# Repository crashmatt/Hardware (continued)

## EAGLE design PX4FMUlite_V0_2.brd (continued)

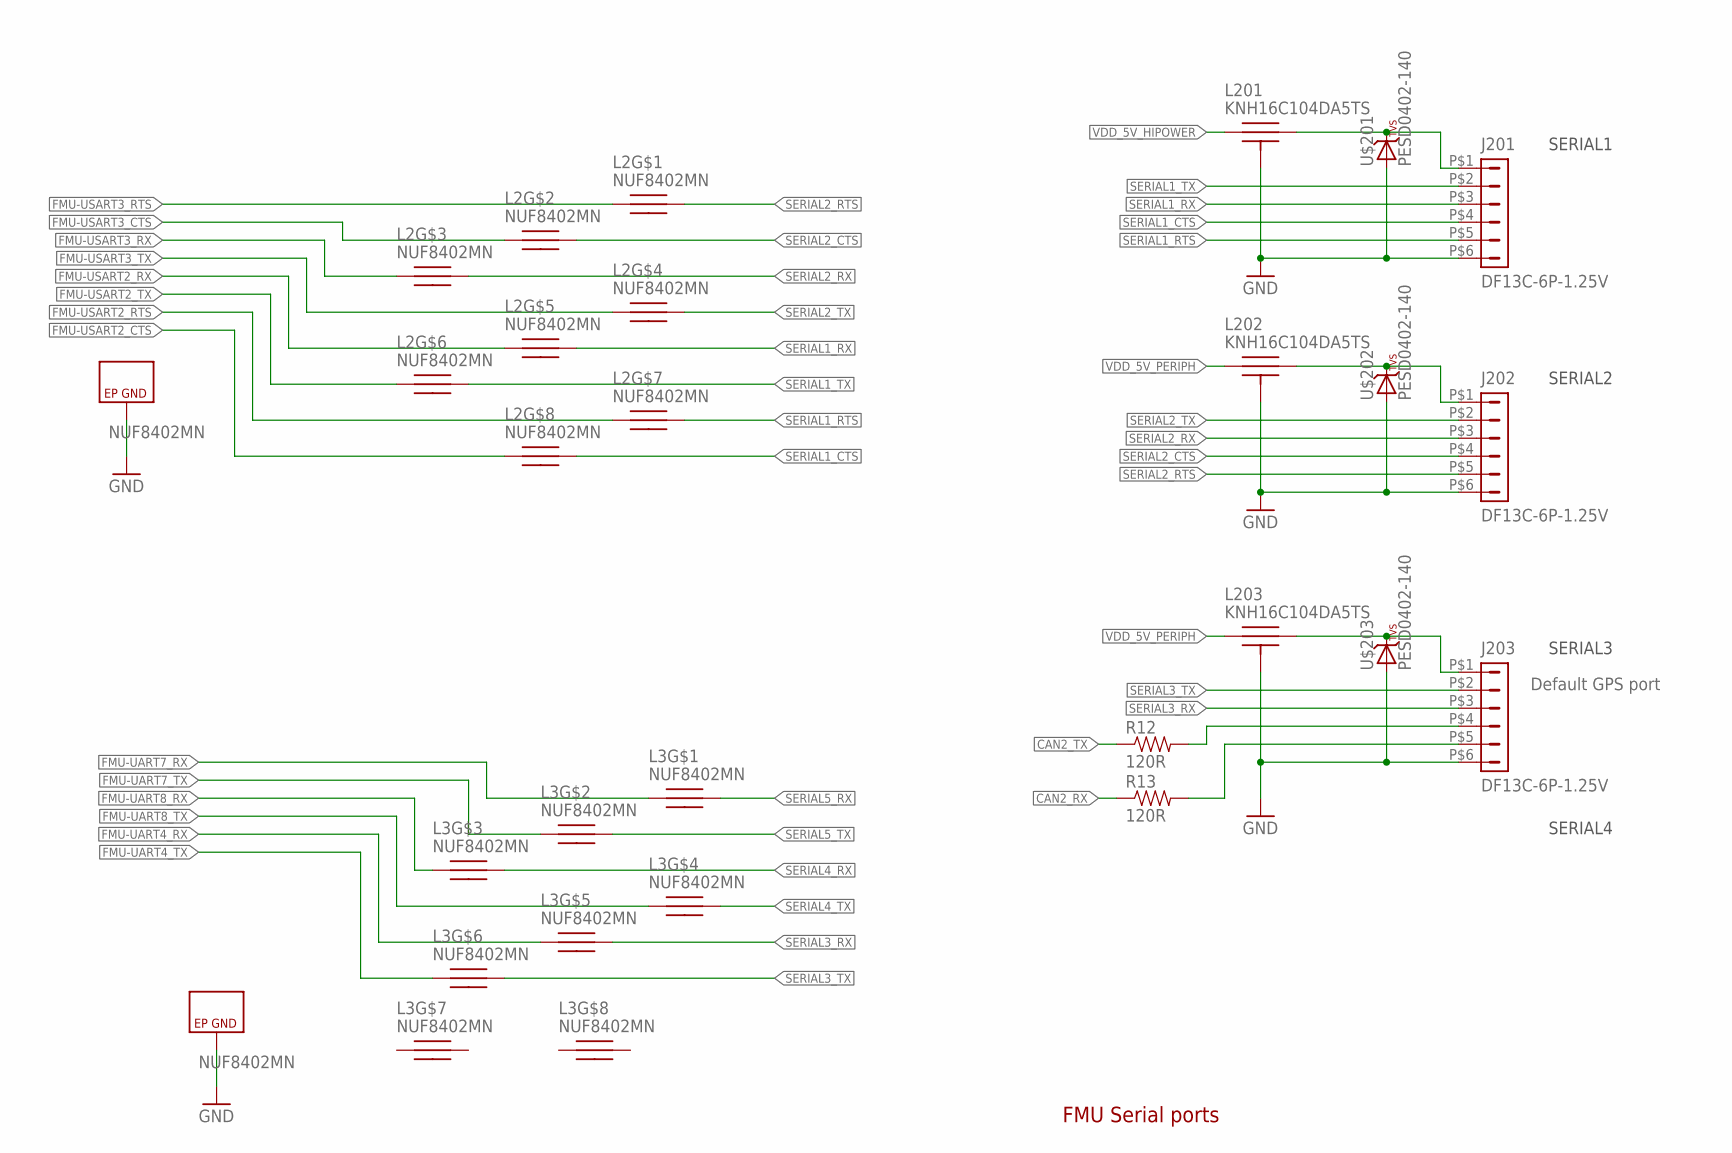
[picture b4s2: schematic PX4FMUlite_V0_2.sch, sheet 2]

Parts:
J201, J202, J203: DF13C-6P-1.25V; PARTNO DF13C-6P-1.25V(20)
L2, L3: NUF8402MN; DFN16-THIN
L201, L202, L203: KNH16C104DA5TS; KYOCERA-KNH16-DA; PARTNO KNH16C104DA5TS
R12, R13: 120R; 0402-RES; PARTNO RC0402FR-07120RL
U$201, U$202, U$203: PESD0402-140; 0402-TVS; PARTNO PESD0402-140

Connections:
CAN2_RX: R13.P$1 (1); also elsewhere on the board
CAN2_TX: R12.P$1 (1); also elsewhere on the board
FMU-UART4_RX: L3.P$5; also elsewhere on the board
FMU-UART4_TX: L3.P$6; also elsewhere on the board
FMU-UART7_RX: L3.P$1; also elsewhere on the board
FMU-UART7_TX: L3.P$2; also elsewhere on the board
FMU-UART8_RX: L3.P$3; also elsewhere on the board
FMU-UART8_TX: L3.P$4; also elsewhere on the board
FMU-USART2_CTS: L2.P$8; also elsewhere on the board
FMU-USART2_RTS: L2.P$7; also elsewhere on the board
FMU-USART2_RX: L2.P$5; also elsewhere on the board
FMU-USART2_TX: L2.P$6; also elsewhere on the board
FMU-USART3_CTS: L2.P$2; also elsewhere on the board
FMU-USART3_RTS: L2.P$1; also elsewhere on the board
FMU-USART3_RX: L2.P$3; also elsewhere on the board
FMU-USART3_TX: L2.P$4; also elsewhere on the board
GND: L2.P$EP (GND), L3.P$EP (GND); also elsewhere on the board
GNDX: J201.P$6 (6), J202.P$6 (6), J203.P$6 (6), L201.P$3, L201.P$4, L201.P$5, L202.P$3, L202.P$4, L202.P$5, L203.P$3, L203.P$4, L203.P$5, U$201.A, U$202.A, U$203.A; also elsewhere on the board
unnamed: J201.P$1 (1), L201.P$2, U$201.C
unnamed: J203.P$4 (4), R12.P$2 (2)
unnamed: J203.P$5 (5), R13.P$2 (2)
unnamed: J203.P$1 (1), L203.P$2, U$203.C
unnamed: J202.P$1 (1), L202.P$2, U$202.C
SERIAL1_CTS: J201.P$4 (4), L2.P$9
SERIAL1_RTS: J201.P$5 (5), L2.P$10
SERIAL1_RX: J201.P$3 (3), L2.P$12; also elsewhere on the board
SERIAL1_TX: J201.P$2 (2), L2.P$11; also elsewhere on the board
SERIAL2_CTS: J202.P$4 (4), L2.P$15
SERIAL2_RTS: J202.P$5 (5), L2.P$16
SERIAL2_RX: J202.P$3 (3), L2.P$14; also elsewhere on the board
SERIAL2_TX: J202.P$2 (2), L2.P$13; also elsewhere on the board
SERIAL3_RX: J203.P$3 (3), L3.P$12; also elsewhere on the board
SERIAL3_TX: J203.P$2 (2), L3.P$11; also elsewhere on the board
SERIAL4_RX: L3.P$14; also elsewhere on the board
SERIAL4_TX: L3.P$13; also elsewhere on the board
SERIAL5_RX: L3.P$16; also elsewhere on the board
SERIAL5_TX: L3.P$15; also elsewhere on the board
VDD_5V_HIPOWER: L201.P$1
VDD_5V_PERIPH: L202.P$1, L203.P$1; also elsewhere on the board

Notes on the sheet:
FMU Serial ports
SERIAL2
SERIAL1
SERIAL3
SERIAL4
Default GPS port

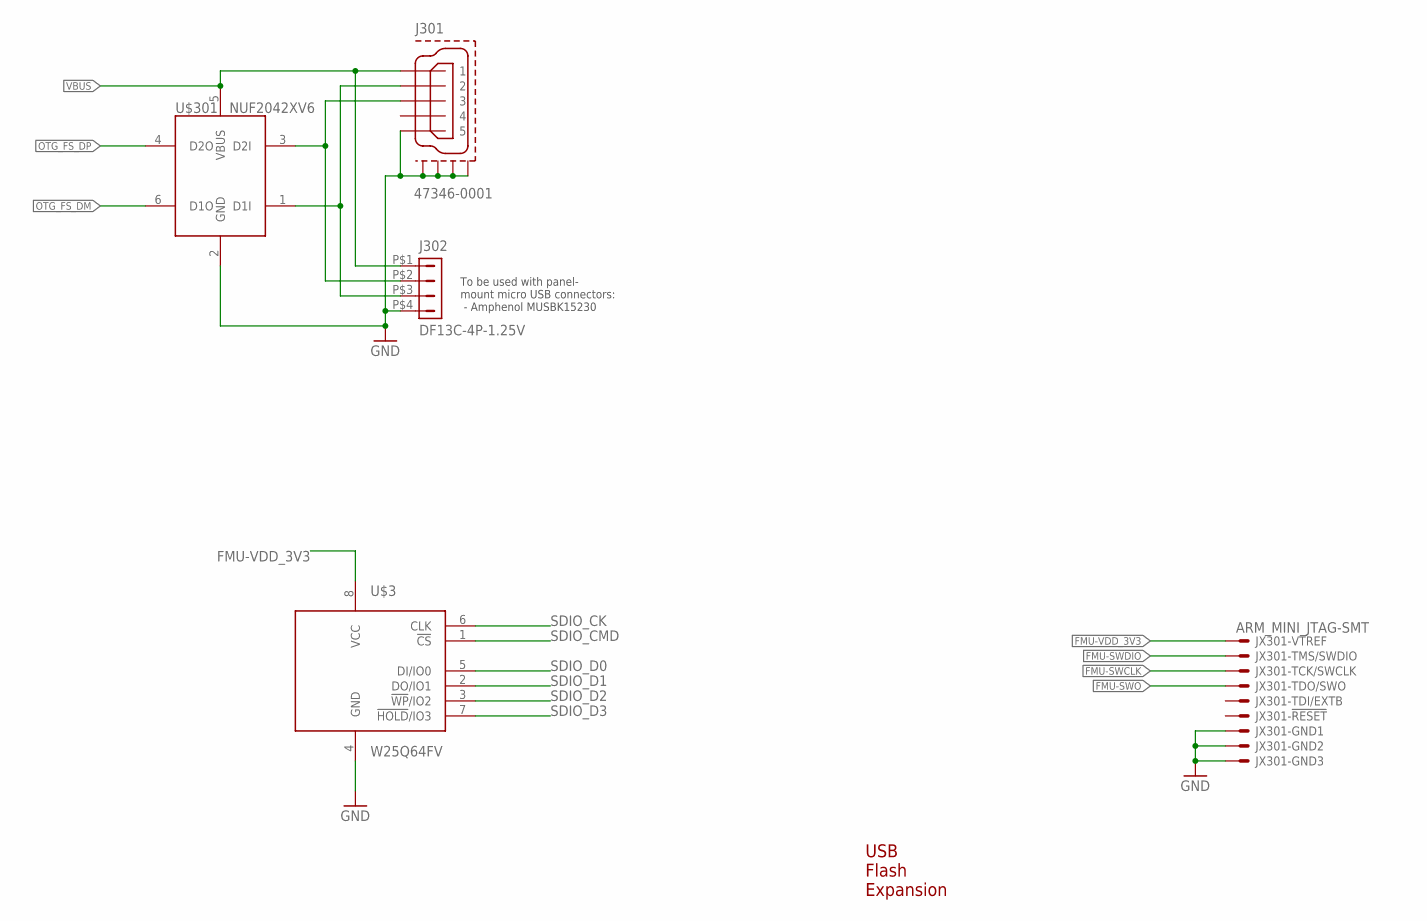
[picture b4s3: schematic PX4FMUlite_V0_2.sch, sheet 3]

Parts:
J301: 47346-0001; MOLEX-47346-0001; PARTNO 47346-0001
J302: DF13C-4P-1.25V; PARTNO DF13C-4P-1.25V(20)
JX301: ARM_MINI_JTAG-SMT; FTSH-105-01-XXX-DV-K; PARTNO M50-3900542
U$3: W25Q64FV; WSON-8-5X6
U$301: NUF2042XV6; SOT563-6; PARTNO NUF2042XV6T1G

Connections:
FMU-SWCLK: JX301.4; also elsewhere on the board
FMU-SWDIO: JX301.2; also elsewhere on the board
FMU-SWO: JX301.6; also elsewhere on the board
FMU-VDD_3V3: JX301.1, U$3.8 (VCC); also elsewhere on the board
GND: U$3.4 (GND); also elsewhere on the board
GNDX: J301.GND (5), J301.GND1, J301.GND2, J301.GND3, J301.GND4, J302.P$4 (4), JX301.3, JX301.5, JX301.9, U$301.2 (GND); also elsewhere on the board
OTG_DM1: J301.D- (2), J302.P$3 (3), U$301.1 (D1I)
OTG_DP1: J301.D+ (3), J302.P$2 (2), U$301.3 (D2I)
OTG_FS_DM: U$301.6 (D1O); also elsewhere on the board
OTG_FS_DP: U$301.4 (D2O); also elsewhere on the board
SDIO_CK: U$3.6 (CLK); also elsewhere on the board
SDIO_CMD: U$3.1 (!CS); also elsewhere on the board
SDIO_D0: U$3.5 (DI/IO0); also elsewhere on the board
SDIO_D1: U$3.2 (DO/IO1); also elsewhere on the board
SDIO_D2: U$3.3 (!WP!/IO2); also elsewhere on the board
SDIO_D3: U$3.7 (!HOLD!/IO3); also elsewhere on the board
VBUS: J301.VBUS (1), J302.P$1 (1), U$301.5 (VBUS); also elsewhere on the board

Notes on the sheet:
USB Flash Expansion
To be used with panel- mount micro USB connectors: - Amphenol MUSBK15230

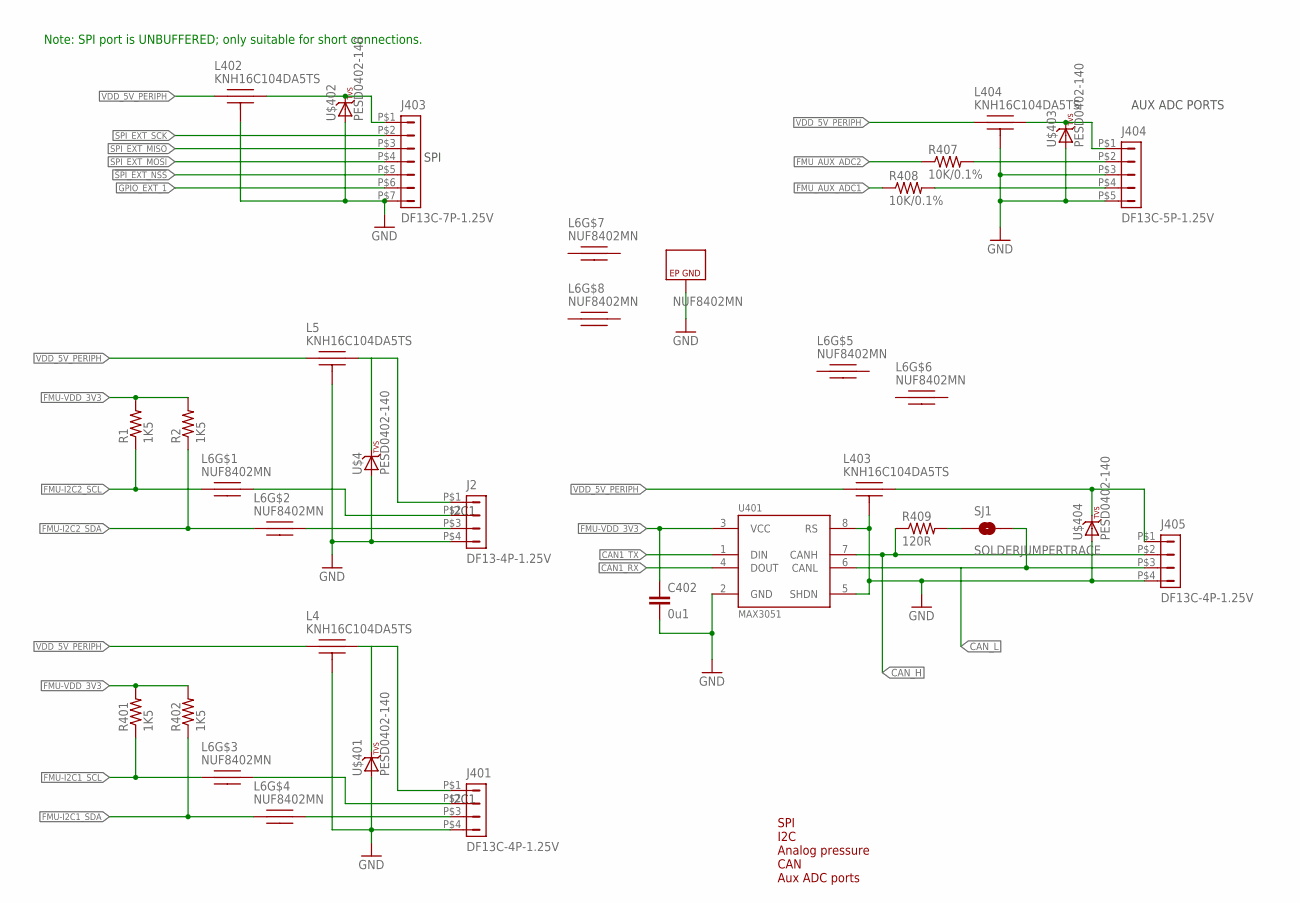
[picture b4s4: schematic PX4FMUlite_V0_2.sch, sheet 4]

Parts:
C402: 0u1; 0402-CAP; PARTNO CC0402ZRY5V7BB104
J2: DF13-4P-1.25V; DF13C-4P-1.25V; PARTNO DF13C-4P-1.25V(20)
J401, J405: DF13C-4P-1.25V; PARTNO DF13C-4P-1.25V(20)
J403: DF13C-7P-1.25V; PARTNO DF13C-7P-1.25V(20)
J404: DF13C-5P-1.25V; PARTNO DF13C-5P-1.25V(20)
L4, L5, L402, L403, L404: KNH16C104DA5TS; KYOCERA-KNH16-DA; PARTNO KNH16C104DA5TS
L6: NUF8402MN; DFN16-THIN
R1, R2, R401, R402: 1K5; 0402-RES; PARTNO RC0402FR-071K5L
R407, R408: 10K/0.1%; 0402-RES; PARTNO ERA-2AEB103X
R409: 120R; 0402-RES; PARTNO RC0402FR-07120RL
SJ1: SOLDERJUMPERTRACE; SJ_2S-TRACE
U401: MAX3051; SOT23-8; PARTNO MAX3051EKA
U$4, U$401, U$402, U$403, U$404: PESD0402-140; 0402-TVS; PARTNO PESD0402-140

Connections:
!SPI_EXT_NSS: J403.P$5 (5); also elsewhere on the board
CAN1_RX: U401.4 (DOUT); also elsewhere on the board
CAN1_TX: U401.1 (DIN); also elsewhere on the board
CAN_H: J405.P$2 (2), R409.P$1 (1), U401.7 (CANH); also elsewhere on the board
CAN_L: J405.P$3 (3), SJ1.2, U401.6 (CANL); also elsewhere on the board
FMU-I2C1_SCL: L6.P$3, R401.P$1 (1); also elsewhere on the board
FMU-I2C1_SDA: L6.P$4, R402.P$1 (1); also elsewhere on the board
FMU-I2C2_SCL: L6.P$1, R1.P$1 (1); also elsewhere on the board
FMU-I2C2_SDA: L6.P$2, R2.P$1 (1); also elsewhere on the board
FMU-VDD_3V3: C402.P$1 (1), R1.P$2 (2), R2.P$2 (2), R401.P$2 (2), R402.P$2 (2), U401.3 (VCC); also elsewhere on the board
FMU_AUX_ADC1: R408.P$1 (1); also elsewhere on the board
FMU_AUX_ADC1_PROT: J404.P$4 (4), R408.P$2 (2)
FMU_AUX_ADC2: R407.P$1 (1); also elsewhere on the board
FMU_AUX_ADC2_PROT: J404.P$2 (2), R407.P$2 (2)
GND: J2.P$4 (4), L5.P$3, L5.P$4, L5.P$5, U$4.A; also elsewhere on the board
GNDX: C402.P$2 (2), J401.P$4 (4), J403.P$7 (7), J404.P$3 (3), J404.P$5 (5), J405.P$4 (4), L4.P$3, L4.P$4, L4.P$5, L6.P$EP (GND), L402.P$3, L402.P$4, L402.P$5, L403.P$3, L403.P$4, L403.P$5, L404.P$3, L404.P$4, L404.P$5, U401.2 (GND), U401.5 (SHDN), U401.8 (RS), U$401.A, U$402.A, U$403.A, U$404.A; also elsewhere on the board
GPIO_EXT_1: J403.P$6 (6); also elsewhere on the board
unnamed: J2.P$2 (2), L6.P$16
unnamed: J2.P$3 (3), L6.P$15
unnamed: J2.P$1 (1), L5.P$2, U$4.C
unnamed: R409.P$2 (2), SJ1.1
unnamed: J401.P$2 (2), L6.P$14
unnamed: J401.P$3 (3), L6.P$13
unnamed: J403.P$1 (1), L402.P$2, U$402.C
unnamed: J401.P$1 (1), L4.P$2, U$401.C
unnamed: J405.P$1 (1), L403.P$2, U$404.C
unnamed: J404.P$1 (1), L404.P$2, U$403.C
SPI_EXT_MISO: J403.P$3 (3); also elsewhere on the board
SPI_EXT_MOSI: J403.P$4 (4); also elsewhere on the board
SPI_EXT_SCK: J403.P$2 (2); also elsewhere on the board
VDD_5V_PERIPH: L402.P$1, L403.P$1, L404.P$1; also elsewhere on the board

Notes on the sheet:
SPI
I2C1
AUX ADC PORTS
SPI I2C Analog pressure CAN Aux ADC ports
Note: SPI port is UNBUFFERED; only suitable for short connections.

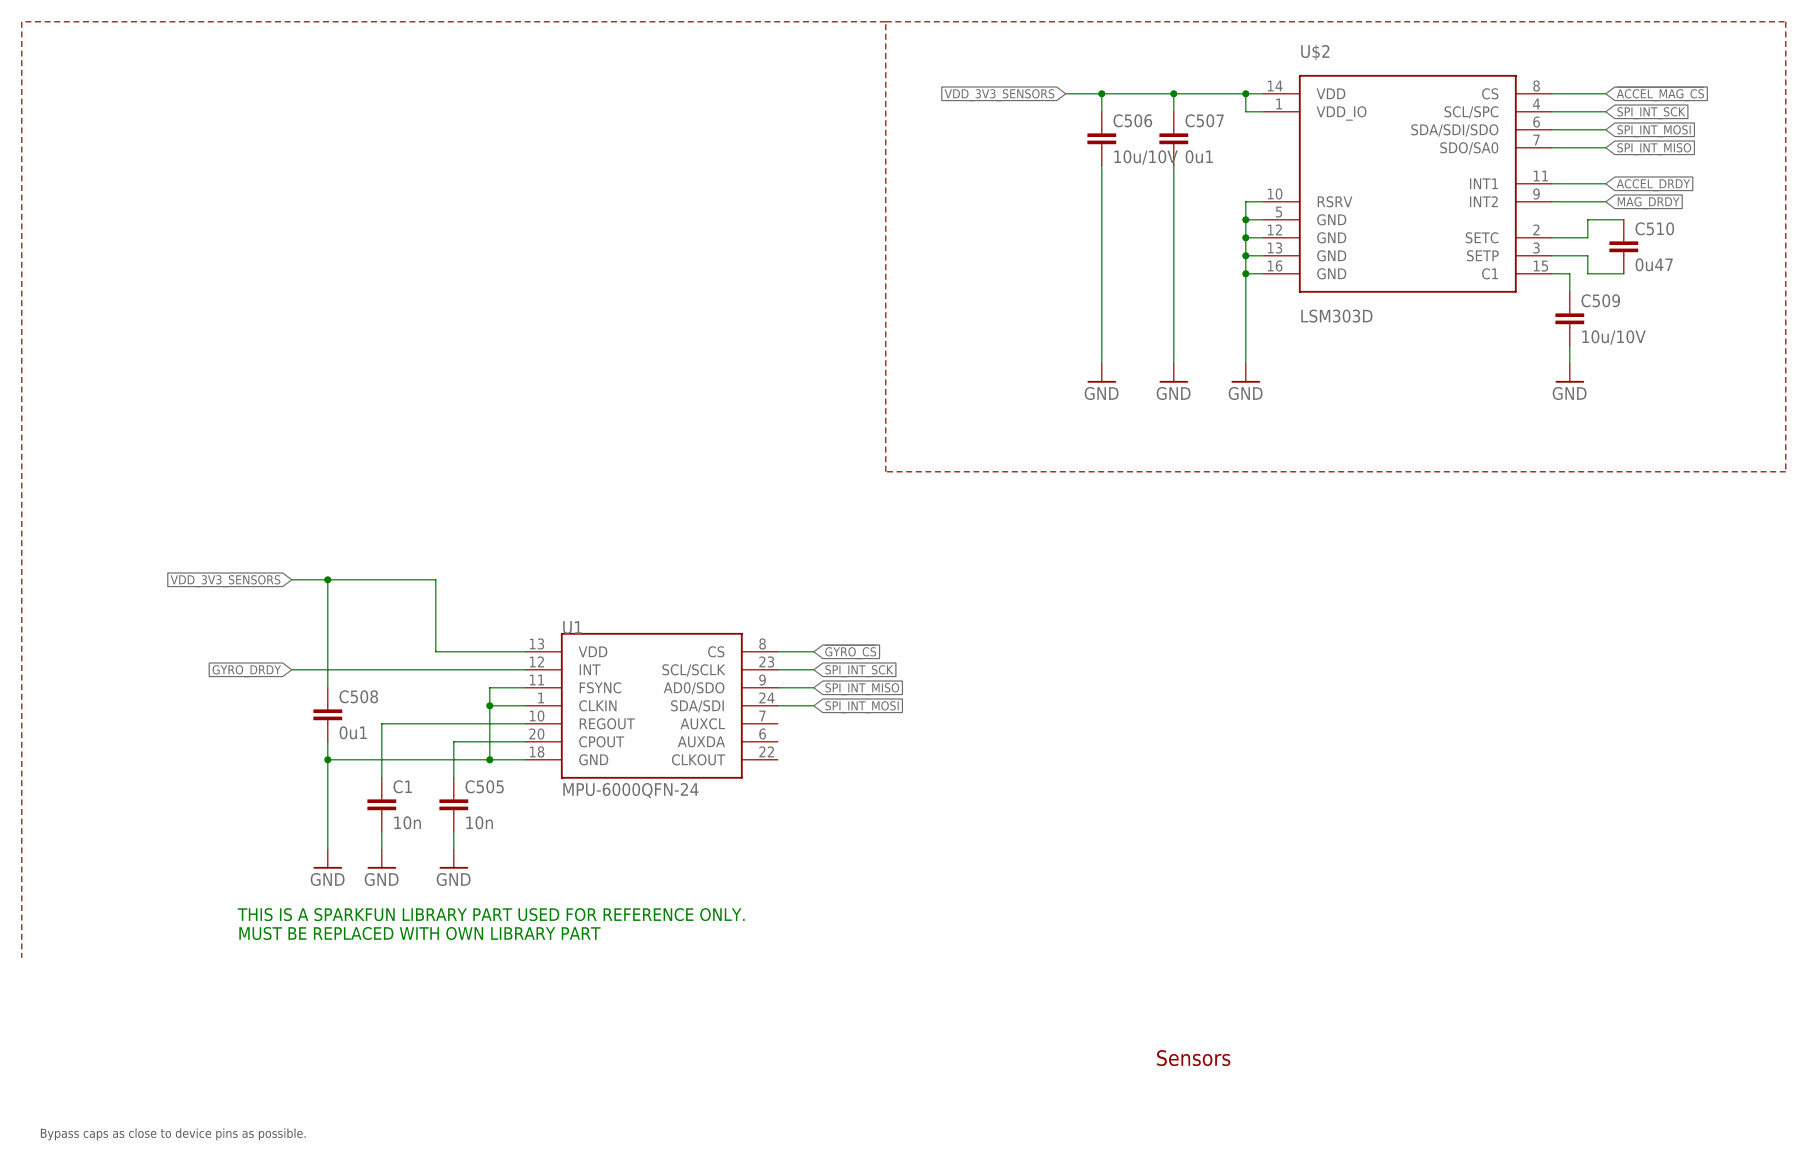
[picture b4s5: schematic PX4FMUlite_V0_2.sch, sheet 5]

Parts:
C1, C505: 10n; 0402-CAP; PARTNO CC0402KRX7R7BB103
C506, C509: 10u/10V; 0805-CAP; PARTNO CC0805ZKY5V6BB106
C507, C508: 0u1; 0402-CAP; PARTNO CC0402ZRY5V7BB104
C510: 0u47; 0402-CAP; PARTNO C1005X5R1C474K050BC
U1: MPU-6000QFN-24; QFN-24-TESTING
U$2: LSM303D; LGA-16L

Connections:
!ACCEL_MAG_CS: U$2.8 (CS); also elsewhere on the board
!GYRO_CS: U1.8 (CS); also elsewhere on the board
ACCEL_DRDY: U$2.11 (INT1); also elsewhere on the board
GND: C1.P$2 (2); also elsewhere on the board
GNDX: C505.P$2 (2), C506.P$2 (2), C507.P$2 (2), C508.P$2 (2), C509.P$2 (2), U1.1 (CLKIN), U1.11 (FSYNC), U1.18 (GND), U$2.5 (GND), U$2.10 (RSRV), U$2.12 (GND), U$2.13 (GND), U$2.16 (GND); also elsewhere on the board
GYRO_DRDY: U1.12 (INT); also elsewhere on the board
MAG_DRDY: U$2.9 (INT2); also elsewhere on the board
unnamed: C509.P$1 (1), U$2.15 (C1)
unnamed: C510.P$1 (1), U$2.2 (SETC)
unnamed: C510.P$2 (2), U$2.3 (SETP)
unnamed: C505.P$1 (1), U1.20 (CPOUT)
unnamed: C1.P$1 (1), U1.10 (REGOUT)
SPI_INT_MISO: U1.9 (AD0/SDO), U$2.7 (SDO/SA0); also elsewhere on the board
SPI_INT_MOSI: U1.24 (SDA/SDI), U$2.6 (SDA/SDI/SDO); also elsewhere on the board
SPI_INT_SCK: U1.23 (SCL/SCLK), U$2.4 (SCL/SPC); also elsewhere on the board
VDD_3V3_SENSORS: C506.P$1 (1), C507.P$1 (1), C508.P$1 (1), U1.13 (VDD), U$2.1 (VDD_IO), U$2.14 (VDD); also elsewhere on the board

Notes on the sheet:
Sensors
Bypass caps as close to device pins as possible.
THIS IS A SPARKFUN LIBRARY PART USED FOR REFERENCE ONLY. MUST BE REPLACED WITH OWN LIBRARY PART

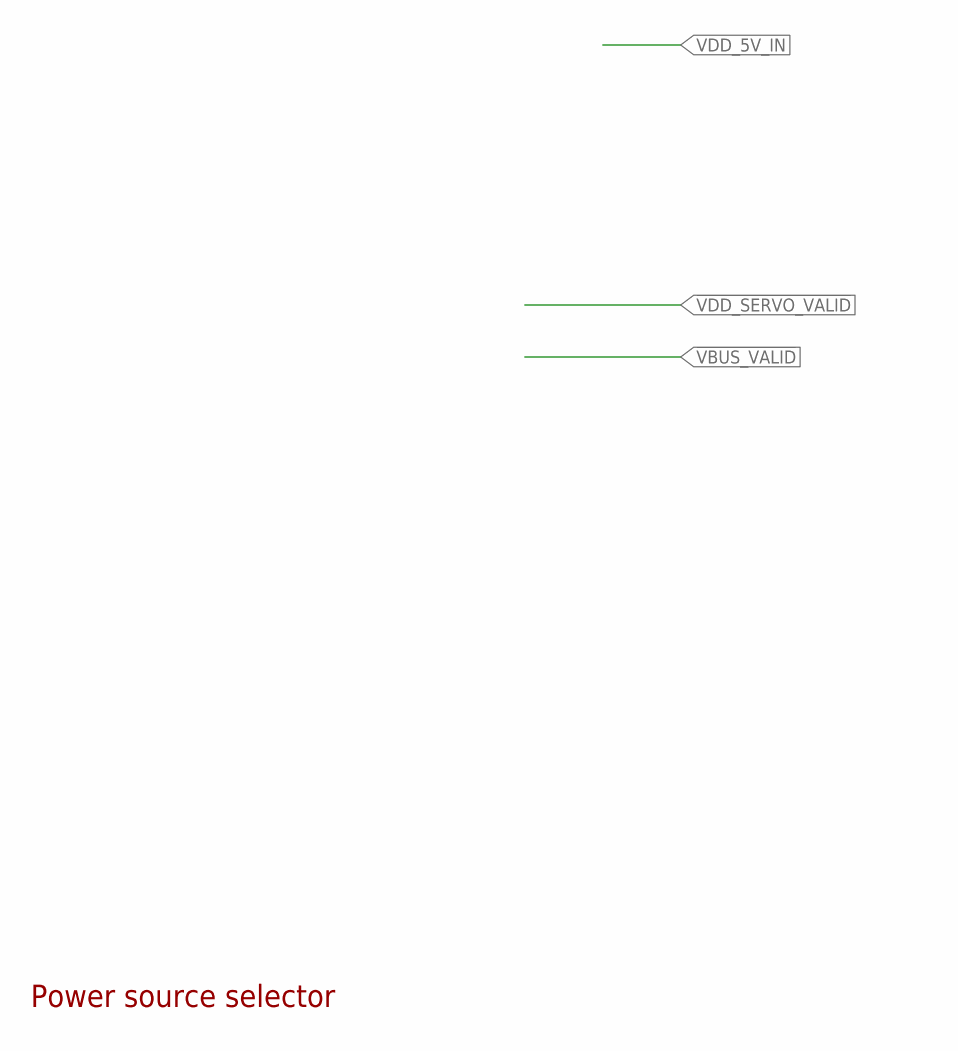
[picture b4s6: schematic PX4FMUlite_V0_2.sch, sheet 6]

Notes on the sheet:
Power source selector

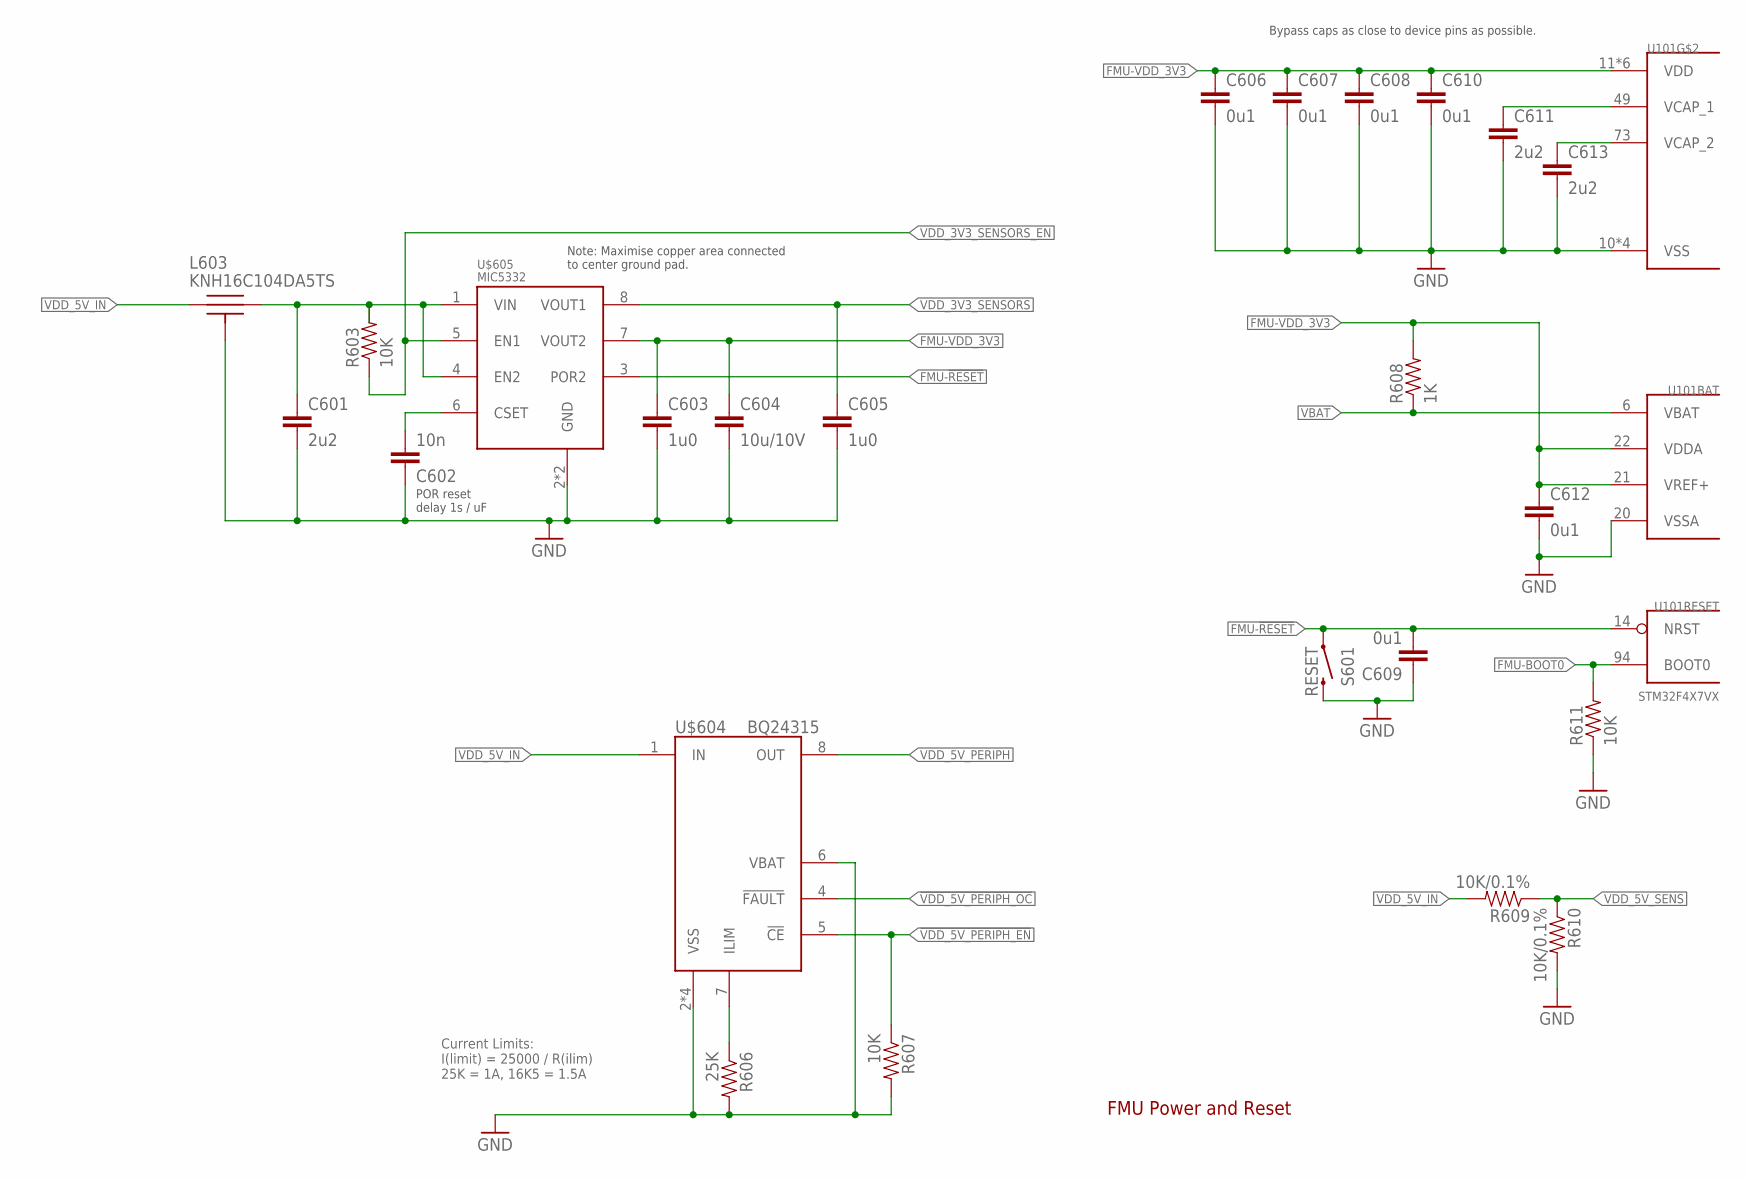
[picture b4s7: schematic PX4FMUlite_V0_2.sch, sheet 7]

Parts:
C601, C611, C613: 2u2; 0603-CAP; PARTNO C1608Y5V1C225Z
C602: 10n; 0402-CAP; PARTNO CC0402KRX7R7BB103
C603, C605: 1u0; 0603-CAP; PARTNO CC0603ZRY5V7BB105
C604: 10u/10V; 0805-CAP; PARTNO CC0805ZKY5V6BB106
C606, C607, C608, C609, C610, C612: 0u1; 0402-CAP; PARTNO CC0402ZRY5V7BB104
L603: KNH16C104DA5TS; KYOCERA-KNH16-DA; PARTNO KNH16C104DA5TS
R603, R607, R611: 10K; 0402-RES; PARTNO RC0402FR-0710KL
R606: 25K; 0402-RES; PARTNO RMCF0402FT25K5
R608: 1K; 0402-RES; PARTNO RC0402FR-071KL
R609, R610: 10K/0.1%; 0402-RES; PARTNO ERA-2AEB103X
S601: RESET; EVQP7J01K; PARTNO EVQP7J01K
U101: STM32F4X7VX; TQFP100; PARTNO STM32F427VI
U$604: BQ24315; QFN8-DSG; PARTNO BQ24315DSGR
U$605: MIC5332; MLF-8-EPAD; PARTNO MIC5332-SSYMT

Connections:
!VDD_5V_PERIPH_EN: R607.P$1 (1), U$604.5 (!CE); also elsewhere on the board
!VDD_5V_PERIPH_OC: U$604.4 (!FAULT); also elsewhere on the board
FMU-!RESET: C609.P$2 (2), S601.A1 (1), U101.14 (NRST), U$605.3 (POR2)
FMU-BOOT0: R611.P$2 (2), U101.94 (BOOT0); also elsewhere on the board
FMU-VDD_3V3: C603.P$1 (1), C604.P$1 (1), C606.P$1 (1), C607.P$1 (1), C608.P$1 (1), C610.P$1 (1), C612.P$1 (1), R608.P$2 (2), U101.11 (VDD), U101.19 (VDD), U101.21 (VREF+), U101.22 (VDDA), U101.28 (VDD), U101.50 (VDD), U101.75 (VDD), U101.100 (VDD), U$605.7 (VOUT2); also elsewhere on the board
FMU-VDD_5V5: C601.P$1 (1), L603.P$2, R603.P$2 (2), U$605.1 (VIN), U$605.4 (EN2)
GNDX: C601.P$2 (2), C602.P$1 (1), C603.P$2 (2), C604.P$2 (2), C605.P$2 (2), C606.P$2 (2), C607.P$2 (2), C608.P$2 (2), C609.P$1 (1), C610.P$2 (2), C611.P$2 (2), C612.P$2 (2), C613.P$2 (2), L603.P$3, L603.P$4, L603.P$5, R606.P$2 (2), R607.P$2 (2), R610.P$2 (2), R611.P$1 (1), S601.B3 (2), U101.10 (VSS), U101.20 (VSSA), U101.27 (VSS), U101.74 (VSS), U101.99 (VSS), U$604.2 (VSS), U$604.6 (VBAT), U$604.GND (VSS), U$604.P$2 (VSS), U$604.P$3 (VSS), U$605.2 (GND), U$605.GND; also elsewhere on the board
unnamed: C613.P$1 (1), U101.73 (VCAP_2)
unnamed: C602.P$2 (2), U$605.6 (CSET)
unnamed: C611.P$1 (1), U101.49 (VCAP_1)
unnamed: R606.P$1 (1), U$604.7 (ILIM)
VBAT: R608.P$1 (1), U101.6 (VBAT)
VDD_3V3_SENSORS: C605.P$1 (1), U$605.8 (VOUT1); also elsewhere on the board
VDD_3V3_SENSORS_EN: R603.P$1 (1), U$605.5 (EN1); also elsewhere on the board
VDD_5V_IN: L603.P$1, R609.P$2 (2), U$604.1 (IN)
VDD_5V_PERIPH: U$604.8 (OUT); also elsewhere on the board
VDD_5V_SENS: R609.P$1 (1), R610.P$1 (1); also elsewhere on the board

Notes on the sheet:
FMU Power and Reset
Bypass caps as close to device pins as possible.
Note: Maximise copper area connected to center ground pad.
POR reset delay 1s / uF
Current Limits: I(limit) = 25000 / R(ilim) 25K = 1A, 16K5 = 1.5A

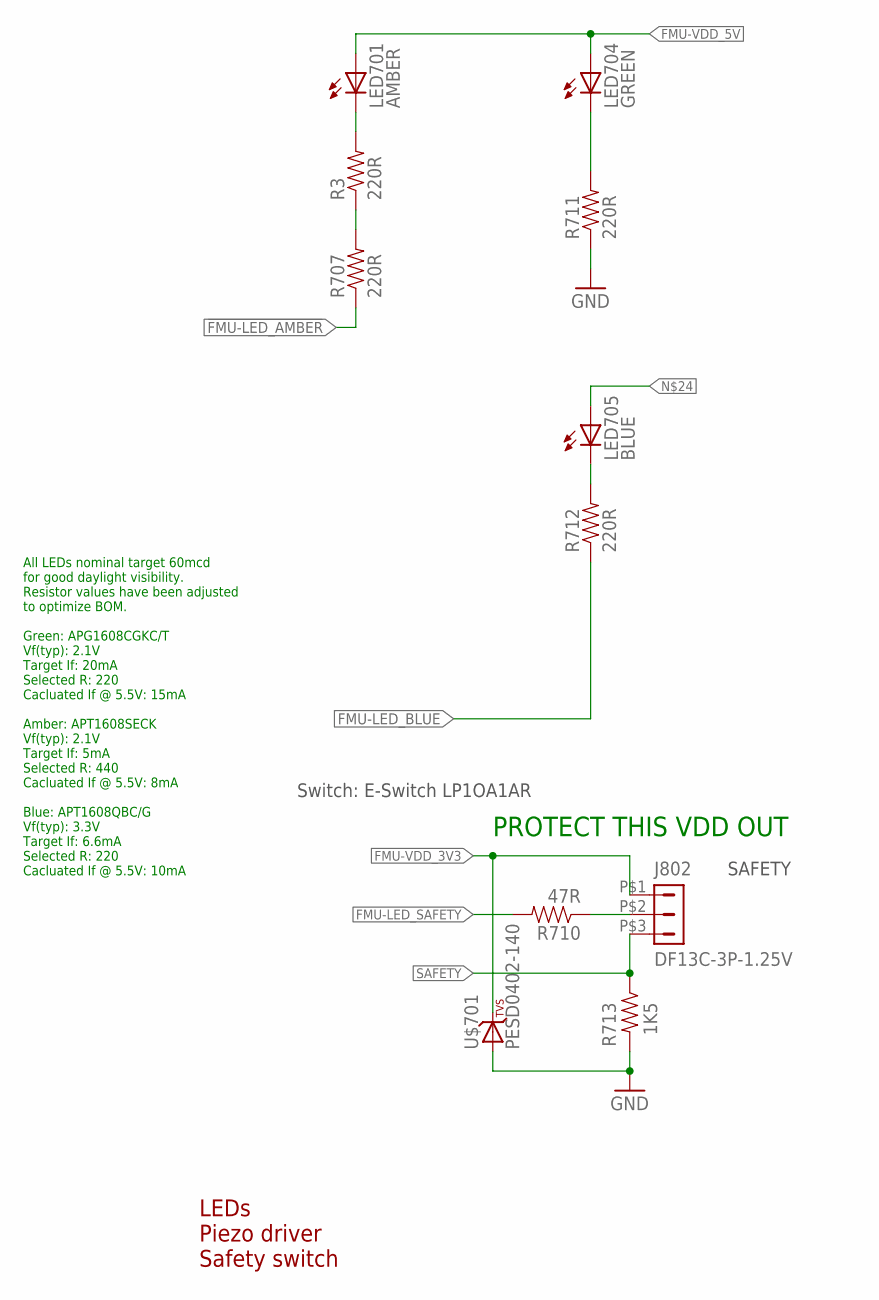
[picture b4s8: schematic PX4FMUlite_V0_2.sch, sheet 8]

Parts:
J802: DF13C-3P-1.25V; PARTNO DF13C-3P-1.25V(20)
LED701: AMBER; 0603-LED; PARTNO APTD1608SECK
LED704: GREEN; 0603-LED; PARTNO APTD1608CGCK
LED705: BLUE; 0603-LED; PARTNO APTD1608QBC/D
R3, R707, R711, R712: 220R; 0402-RES; PARTNO RC0402FR-07220RL
R710: 47R; 0402-RES; PARTNO RC0402JR-0747RL
R713: 1K5; 0402-RES; PARTNO RC0402FR-071K5L
U$701: PESD0402-140; 0402-TVS; PARTNO PESD0402-140

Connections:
!FMU-LED_AMBER: R707.P$1 (1); also elsewhere on the board
FMU-LED_BLUE: R712.P$1 (1)
FMU-LED_SAFETY: R710.P$2 (2)
FMU-VDD_3V3: J802.P$1 (1), U$701.C; also elsewhere on the board
FMU-VDD_5V: LED701.A, LED704.A; also elsewhere on the board
GNDX: R711.P$1 (1), R713.P$2 (2), U$701.A; also elsewhere on the board
unnamed: LED704.C, R711.P$2 (2)
unnamed: LED705.C, R712.P$2 (2)
unnamed: R3.P$1 (1), R707.P$2 (2)
unnamed: LED701.C, R3.P$2 (2)
unnamed: J802.P$2 (2), R710.P$1 (1)
SAFETY: J802.P$3 (3), R713.P$1 (1)

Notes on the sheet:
LEDs Piezo driver Safety switch
Switch: E-Switch LP1OA1AR
SAFETY
All LEDs nominal target 60mcd for good daylight visibility. Resistor values have been adjusted to optimize BOM. Green: APG1608CGKC/T Vf(typ): 2.1V Target If: 20mA Selected R: 220 Cacluated If @ 5.5V: 15mA Amber: APT1608SECK Vf(typ): 2.1V Target If: 5mA Selected R: 440 Cacluated If @ 5.5V: 8mA Blue: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
PROTECT THIS VDD OUT

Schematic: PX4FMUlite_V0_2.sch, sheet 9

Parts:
J801: JST-ZH-3; JST-ZH-SMT-VERTICAL; PARTNO B3B-ZR-SM4-TF (LF)(SN)(P)
JX801: HEADER-3X1BOARDEDGE-SHORT; HEADER_3X01_SMD_H_BOARD_EDGE_SHORT
U$801: PESD0402-140; 0402-TVS; PARTNO PESD0402-140

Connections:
GNDX: J801.P$2, JX801.3 (GND), U$801.A; also elsewhere on the board
IO-USART1_RX: J801.P$3, JX801.2 (+5V)
IO-USART1_TX: JX801.1 (PPM); also elsewhere on the board
VDD_3V3_SPEKTRUM: J801.P$1, U$801.C; also elsewhere on the board

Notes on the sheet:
IO SoC Ports Spektrum/DSM port
IO_SERIAL1
Spektrum/DSM
Timer allocation: PA0: TIM2_CH1: IO-CH1 PA1: TIM2_CH2: IO-CH2 PB8: TIM4_CH3: IO-CH3 PB9: TIM4_CH4: IO-CH4 PA6: TIM3_CH1: IO-CH5 PA7: TIM3_CH2: IO-CH6 PB0: TIM3_CH3: IO-CH7 PB1: TIM3_CH4: IO-CH8 PA8: TIM1_CH1: PPM_IN PA11: TIM1_CH4: RSSI_IN

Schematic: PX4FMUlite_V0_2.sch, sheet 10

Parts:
C901: 0u1; 0402-CAP; PARTNO CC0402ZRY5V7BB104
D1: MSS1P4-M3; MICROSMP; PARTNO MSS1P4-M3/89A
J1: HEADER-3X10; 3X10RA
L1: NUF8402MN; DFN16-THIN
L901: KNH16C104DA5TS; KYOCERA-KNH16-DA; PARTNO KNH16C104DA5TS
R901: 10K; 0402-RES; PARTNO RC0402FR-0710KL
R909, R910: 220R; 0402-RES; PARTNO RC0402FR-07220RL
R918, R919, R922: 10K/0.1%; 0402-RES; PARTNO ERA-2AEB103X
U903: 74LVC2G240; TSSOP8_SOT505-2; PARTNO 74LVC2G240DP,125
U$6, U$901, U$902: PESD0402-140; 0402-TVS; PARTNO PESD0402-140

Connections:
!SBUS_OUTPUT_EN: U903.7 (!2OE)
FMU-CH1: L1.P$1; also elsewhere on the board
FMU-CH1-PROT: J1.1, L1.P$16
FMU-CH2: L1.P$2; also elsewhere on the board
FMU-CH3: L1.P$3; also elsewhere on the board
FMU-CH4: L1.P$4; also elsewhere on the board
FMU-CH5: L1.P$5; also elsewhere on the board
FMU-CH8: L1.P$6; also elsewhere on the board
GND: L1.P$EP (GND); also elsewhere on the board
GNDX: C901.P$2 (2), J1.3, J1.6, J1.9, J1.12, J1.15, J1.18, J1.21, J1.24, J1.27, J1.30, L901.P$3, L901.P$4, L901.P$5, R919.P$1 (1), U903.1 (!1OE), U903.4 (GND), U$6.A, U$901.A, U$902.A; also elsewhere on the board
IO-VDD_3V3: C901.P$1 (1), U903.8 (VCC); also elsewhere on the board
unnamed: R918.P$2 (2), R922.P$1 (1)
unnamed: J1.22, L1.P$9
unnamed: J1.19, L1.P$10
unnamed: J1.16, L1.P$11
unnamed: R901.P$2 (2), R910.P$1 (1), U903.3 (2Y), U$902.C
unnamed: J1.13, L1.P$12
unnamed: J1.10, L1.P$13
unnamed: J1.7, L1.P$14
unnamed: J1.4, L1.P$15
unnamed: D1.CATHODE (C), L901.P$1, U$6.C
PPM-SBUS-PROT: R909.P$2 (2)
PPM_INPUT: R909.P$1 (1), U903.2 (1A), U$901.C
RSSI_IN: R901.P$1 (1)
SBUS_INPUT: U903.6 (1Y)
SBUS_OUTPUT: U903.5 (2A)
VDD_SERVO: D1.ANODE (A), J1.2, J1.5, J1.8, J1.11, J1.14, J1.17, J1.20, J1.23, J1.26, J1.29, R922.P$2 (2)
VDD_SERVO_IN: L901.P$2
VDD_SERVO_SENS: R918.P$1 (1), R919.P$2 (2)

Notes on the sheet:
Servo Header S.Bus interface
S.Bus in/out
Servo outputs

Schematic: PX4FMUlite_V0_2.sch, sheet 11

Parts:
C1001, C1003, C1004: 1u0; 0603-CAP; PARTNO CC0603ZRY5V7BB105
C1002: 10n; 0402-CAP; PARTNO CC0402KRX7R7BB103
R1002: 10K; 0402-RES; PARTNO RC0402FR-0710KL
U$1002: MIC5332; MLF-8-EPAD; PARTNO MIC5332-SSYMT

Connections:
FMU-VDD_5V: C1001.P$1 (1), U$1002.1 (VIN), U$1002.4 (EN2); also elsewhere on the board
GNDX: C1001.P$2 (2), C1002.P$2 (2), C1003.P$2 (2), C1004.P$2 (2), R1002.P$1 (1), U$1002.2 (GND), U$1002.GND; also elsewhere on the board
IO-!RESET: U$1002.3 (POR2)
IO-VDD_3V3: C1004.P$1 (1), U$1002.7 (VOUT2); also elsewhere on the board
unnamed: C1002.P$1 (1), U$1002.6 (CSET)
VDD_3V3_SPEKTRUM: C1003.P$1 (1), U$1002.8 (VOUT1); also elsewhere on the board
VDD_3V3_SPEKTRUM_EN: R1002.P$2 (2), U$1002.5 (EN1)

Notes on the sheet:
IO Power Supply
Reset output 1s / uF 10n = 10ms delay from power good to reset de-asserted.

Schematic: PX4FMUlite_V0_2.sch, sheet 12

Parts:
ADC_PR: PAD.04; PAD.04X.04; PARTNO *
CAN_H: PAD.04; PAD.04X.04; PARTNO *
CAN_L: PAD.04; PAD.04X.04; PARTNO *
FMU-BOOT1101: PAD.04; PAD.04X.04; PARTNO *
GND, GND.: PAD.04; PAD.04X.04; PARTNO *
IO-BOOT1101: PAD.04; PAD.04X.04; PARTNO *
JP1, JP2: FIDUCIAL1.5X3; FIDUCIAL-1.5X3; PARTNO *
M3_MOUNT1101, M3_MOUNT1102, M3_MOUNT1103, M3_MOUNT1104: MOUNT-HOLE3.1MM; MOUNT-HOLE3.1; PARTNO *
OSHW_LOGO: OSHW-LOGOS; OSHW-LOGO-S; PARTNO *
S1RX, S1TX, S2RX, S2TX, S3RX, S3TX, S4RX, S4TX, S5_RX, S5_TX: PAD.04; PAD.04X.04; PARTNO *
VDDA_3V1101: PAD.04; PAD.04X.04; PARTNO *
VDD_3V1101, VDD_5V_BRICK: PAD.04; PAD.04X.04; PARTNO *

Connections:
CAN_H: CAN_H.P$1; also elsewhere on the board
CAN_L: CAN_L.P$1; also elsewhere on the board
FMU-BOOT0: FMU-BOOT1101.P$1; also elsewhere on the board
FMU-VDD_3V3: VDD_3V1101.P$1; also elsewhere on the board
GNDX: GND.P$1, GND..P$1; also elsewhere on the board
IO-BOOT0: IO-BOOT1101.P$1
PRESSURE_SENS_IN: ADC_PR.P$1
SERIAL1_RX: S1RX.P$1; also elsewhere on the board
SERIAL1_TX: S1TX.P$1; also elsewhere on the board
SERIAL2_RX: S2RX.P$1; also elsewhere on the board
SERIAL2_TX: S2TX.P$1; also elsewhere on the board
SERIAL3_RX: S3RX.P$1; also elsewhere on the board
SERIAL3_TX: S3TX.P$1; also elsewhere on the board
SERIAL4_RX: S4RX.P$1; also elsewhere on the board
SERIAL4_TX: S4TX.P$1; also elsewhere on the board
SERIAL5_RX: S5_RX.P$1; also elsewhere on the board
SERIAL5_TX: S5_TX.P$1; also elsewhere on the board
VDD_3V3_SENSORS: VDDA_3V1101.P$1; also elsewhere on the board
VDD_5V_BRICK: VDD_5V_BRICK.P$1

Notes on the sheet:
Mounting holes to suit M3 fastener
and Richco R908 series spacer.
Use R908-5 spacers to stack with
other PX4 series boards (7.95 mm).
Production Testing Pads
Test and Fiducials
Minimum drill: 0.3 mm
Minimum trace width (use mm for traces): 0.15 mm
Minimum copper distance (all signals): 0.15 mm
Dimension / hole minimum distance: 0.2 mm
Layout grid: 4 mil, part grid: 4 mil. Dimensions / hole positions: 0.5 mm
Board: FR4 black, 1.0 mm. Solder stop on vias < 0.6 mm.
Signoff rules: Footprint checked, pinmap checked, schematic checked, cross-references to other pages checked.
Routing: 1: general/escape 2: ground 3: horizontal 4: vertical 5: power 6: general/escape
Fiducials for machine vision alignment.
